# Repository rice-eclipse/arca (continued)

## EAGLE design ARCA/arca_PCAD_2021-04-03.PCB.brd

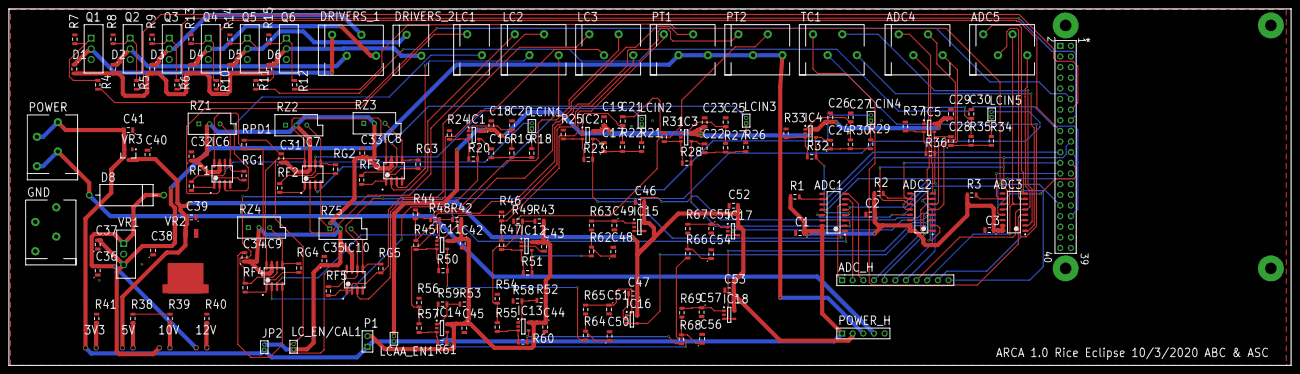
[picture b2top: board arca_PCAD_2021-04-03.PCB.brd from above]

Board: 2 copper layers, 306.1 x 85.1 mm, 197 parts (0 on the bottom side), 114 nets.

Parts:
3V3: LED5MM; LED5MM_1PRIMARY
5V: LED5MM; LED5MM_4PRIMARY
10V: LED5MM; LED5MM_3PRIMARY
12V: LED5MM; LED5MM_2PRIMARY
*: raspberry_pi; HDR2X20_1PRIMARY
ADC1, ADC2, ADC3: MCP3208; SOIC127P600X175-16N_1PRIMARY
ADC4, ADC5: PTSA_1,5/_4-3,5-Z_-_1985218; 4PINCANCONNECTOR_1PRIMARY
ADC_H: Header_11; HDR1X11_1PRIMARY
C1, C2, C3, C39: Cap; CAPCP2012X06N_3PRIMARY
C16: 1nF; CAPCP2012X06N_16PRIMARY
C17, C21, C22, C24: 1nF; CAPCP2012X06N_14PRIMARY
C18: 0.1UF; CAPCP2012X06N_15PRIMARY
C19, C23, C26: 0.1UF; CAPCP2012X06N_14PRIMARY
C20: 1nF; CAPCP2012X06N_15PRIMARY
C25, C27: 1nF; CAPCP2012X06N_13PRIMARY
C28: 1nF; CAPCP2012X06N_11PRIMARY
C29: 0.1UF; CAPCP2012X06N_11PRIMARY
C30: 1nF; CAPCP2012X06N_12PRIMARY
C31: 1UF; CAPCP2012X06N_11PRIMARY
C32: 1UF; CAPCP2012X06N_2PRIMARY
C33: 1UF; CAPCP2012X06N_10PRIMARY
C34: 1UF; CAPCP2012X06N_9PRIMARY
C35: 1UF; CAPCP2012X06N_8PRIMARY
C36, C37, C38: Cap; CAPCP2012X06N_2PRIMARY
C40: Cap; CAPCP2012X06N_7PRIMARY
C41: Cap; CAPCP2012X06N_6PRIMARY
C42, C43, C44, C45: 0.1UF; CAPCP2012X06N_1PRIMARY
C46: 0.1UF; CAPCP2012X06N_5PRIMARY
C47, C52, C53: 0.1UF; CAPCP2012X06N_3PRIMARY
C48: 68nF; CAPCP2012X06N_4PRIMARY
C49, C51, C55, C57: 680pF; CAPCP2012X06N_1PRIMARY
C50, C54, C56: 68nF; CAPCP2012X06N_2PRIMARY
D1, D2, D3, D4, D5, D6: Diode; DIOC2012X06N_1PRIMARY
D8: Diode; DIODE-0.7_1PRIMARY
DRIVERS_1: 1991118; 4PINCANCONNECTOR_1PRIMARY
DRIVERS_2: 0; 2POS_GREEN_BOI_1PRIMARY
DUMMY1, DUMMY2, DUMMY3, DUMMY4: P:EX244Y244D1081
GND: 1991118; 4PINCANCONNECTOR_1PRIMARY
IC1, IC2, IC4: LMV321LICTRT; SOT95P245X110-5N_6PRIMARY
IC3: LMV321LICTRT; SOT95P245X110-5N_7PRIMARY
IC5: LMV321LICTRT; SOT95P245X110-5N_5PRIMARY
IC6, IC8, IC9, IC10: MCP6N11R; SOIC127P1030X265-8N_1PRIMARY
IC7: MCP6N11R; SOIC127P1030X265-8N_2PRIMARY
IC11: LMV321LICTRT; SOT95P245X110-5N_4PRIMARY
IC12, IC13, IC14, IC15, IC17: LMV321LICTRT; SOT95P245X110-5N_2PRIMARY
IC16: LMV321LICTRT; SOT95P245X110-5N_3PRIMARY
IC18: LMV321LICTRT; SOT95P245X110-5N_1PRIMARY
JP2: PINHD-1X2; MHDR1X2_4PRIMARY
LC1: 0; 2POS_GREEN_BOI_2PRIMARY
LC2: 1991118; 4PINCANCONNECTOR_6PRIMARY
LC3: 1991118; 4PINCANCONNECTOR_5PRIMARY
LCAA_EN1: PINHD-1X2; MHDR1X2_3PRIMARY
LCIN1: PINHD-1X2; MHDR1X2_4PRIMARY
LCIN2, LCIN3: PINHD-1X2; MHDR1X2_3PRIMARY
LCIN4: PINHD-1X2; MHDR1X2_2PRIMARY
LCIN5: PINHD-1X2; MHDR1X2_1PRIMARY
LC_EN/CAL1: PINHD-1X2; MHDR1X2_4PRIMARY
P1: Header_2; HDR1X2_1PRIMARY
POWER: 1991118; 4PINCANCONNECTOR_1PRIMARY
POWER_H: Header_5; HDR1X5_1PRIMARY
PT1: 1991118; 4PINCANCONNECTOR_4PRIMARY
PT2: 1991118; 4PINCANCONNECTOR_3PRIMARY
Q1, Q2, Q3, Q4, Q5, Q6: FQP30N06L-ND; UA78M_1PRIMARY
R1, R2, R3: Res1; RESC_0805_2012_6PRIMARY
R4, R5, R6, R10, R11, R12: Res1; RESC_0805_2012_8PRIMARY
R7: Res1; RESC_0805_2012_1PRIMARY
R8, R9, R13, R14, R15: Res1; RESC_0805_2012_17PRIMARY
R18: 24.7K; RESC_0805_2012_11PRIMARY
R19: 164K; RESC_0805_2012_16PRIMARY
R20: 50.6K; RESC_0805_2012_8PRIMARY
R21: 24.7K; RESC_0805_2012_15PRIMARY
R22: 164K; RESC_0805_2012_14PRIMARY
R23, R28, R32, R36: 50.6K; RESC_0805_2012_6PRIMARY
R24, R25, R37: 12.6K; RESC_0805_2012_2PRIMARY
R26: 24.7K; RESC_0805_2012_2PRIMARY
R27: 164K; RESC_0805_2012_1PRIMARY
R29: 24.7K; RESC_0805_2012_13PRIMARY
R30: 164K; RESC_0805_2012_12PRIMARY
R31, R33: 12.6K; RESC_0805_2012_11PRIMARY
R34: 24.7K; RESC_0805_2012_10PRIMARY
R35: 164K; RESC_0805_2012_9PRIMARY
R38: 140; RESC_0805_2012_2PRIMARY
R39: 470; RESC_0805_2012_1PRIMARY
R40: 530; RESC_0805_2012_1PRIMARY
R41: 39; RESC_0805_2012_2PRIMARY
R42, R43, R53: 20K; RESC_0805_2012_6PRIMARY
R44, R46, R56: 22; RESC_0805_2012_1PRIMARY
R45, R47, R55, R57: 20K; RESC_0805_2012_2PRIMARY
R48, R49, R58, R59: 3K; RESC_0805_2012_6PRIMARY
R50, R51, R60, R61: 150K; RESC_0805_2012_6PRIMARY
R52: 20K; RESC_0805_2012_8PRIMARY
R54: 22; RESC_0805_2012_7PRIMARY
R62, R64, R66, R68: 1.5K; RESC_0805_2012_1PRIMARY
R63, R65, R67, R69: 150K; RESC_0805_2012_1PRIMARY
RF1, RF3, RF4: 20K; RESC_0805_2012_1PRIMARY
RF2: 20K; RESC_0805_2012_4PRIMARY
RF5: 20K; RESC_0805_2012_5PRIMARY
RG1, RG3, RG4: 200; RESC_0805_2012_1PRIMARY
RG2: 200; RESC_0805_2012_4PRIMARY
RG5: 200; RESC_0805_2012_3PRIMARY
RPD1: 20K; RESC_0805_2012_2PRIMARY
RZ1, RZ3, RZ4: RPot; VR5_2PRIMARY
RZ2: RPot; VR5_3PRIMARY
RZ5: RPot; VR5_1PRIMARY
TC1: 1991118; 4PINCANCONNECTOR_2PRIMARY
VR1: UA78M; UA78M_1PRIMARY
VR2: LM1084ISX-5.0/NOPB; LM1084ISX-5.0/NOPB_1PRIMARY
VR3: AP2210N-3.3TRG1; SOT95P245X110-3N_1PRIMARY

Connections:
+3V3: 3V3.1, C1.1, JP2.1, LCAA_EN1.1, P1.1
+3V3_LC: C31.1, C32.1, C33.1, C34.1, C35.1, IC6.7, IC7.7, IC8.7, IC9.7, IC10.7, JP2.2, LC_EN/CAL1.1, RZ1.2, RZ2.2, RZ3.2, RZ4.2, RZ5.2
+3V3_LCAA: C18.1, C19.1, C23.1, C26.1, C29.1, IC1.5, IC2.5, IC3.5, IC4.5, IC5.5, LCAA_EN1.2
+3V3_PT: C42.1, C43.1, C44.1, C45.1, IC11.5, IC12.5, IC13.5, IC14.5, P1.2, R42.1, R43.1, R52.1, R53.1
+5V: 5V.1, C39.2, C40.2, C46.1, C47.1, C52.1, C53.1, IC15.5, IC16.5, IC17.5, IC18.5, POWER_H.2, VR2.2, VR3.3
+10V: 10V.1, C37.2, C38.2, POWER_H.3, VR1.3
+12: D1.2, D2.2, D3.2, D4.2, D5.2, D6.2
ADC1_A5: ADC1.6, ADC_H.1
ADC1_A6: ADC1.7, ADC_H.2
ADC1_A7: ADC1.8, ADC_H.3
ADC1_CS: *.22, ADC1.10, R1.1
ADC2_A4: ADC2.5, ADC_H.4
ADC2_A7: ADC2.8, ADC_H.7
ADC2_CS: *.24, ADC2.10, R2.1
ADC3_A4: ADC3.5, ADC_H.8
ADC3_CS: *.26, ADC3.10, R3.1
CAL: IC6.8, IC7.8, IC8.8, IC9.8, IC10.8, LC_EN/CAL1.2, RPD1.1
DRIVER_1: *.11, R4.1
DRIVER_1_NEGATIVE: D1.1, Q1.2
DRIVER_2: *.13, R5.1
DRIVER_2_NEGATIVE: D2.1, Q2.2
DRIVER_3: *.15, R6.1
DRIVER_3_NEGATIVE: D3.1, Q3.2
DRIVER_4: *.18, R10.1
DRIVER_4_NEGATIVE: D4.1, Q4.2
DRIVER_5: *.33, R11.1
DRIVER_5_NEGATIVE: D5.1, DRIVERS_2.1, Q5.2
DRIVER_6: *.32, R12.1
DRIVER_6_NEGATIVE: D6.1, DRIVERS_2.2, Q6.2
GND: C36.1, C38.1, GND.1, GND.2, GND.3, GND.4, R38.2, R39.1, R40.1, R41.2
LC1: ADC1.1, C16.2, IC1.4, R20.1
LC1_OUT_N: IC6.2, LC1.1
LC1_OUT_P: IC6.3, LC1.2
LC1_PREC: IC6.6, LCIN1.2, RF1.1
LC2: ADC1.2, C17.2, IC2.4, R23.1
LC2_PREC: IC7.6, LCIN2.2, RF2.1
LC3: ADC1.3, C22.2, IC3.4, R28.1
LC3_PREC: IC8.6, LCIN3.2, RF3.1
LC4: ADC1.4, C24.2, IC4.4, R32.1
LC4_PREC: IC9.6, LCIN4.2, RF4.1
LC5: ADC1.5, C28.2, IC5.4, R36.1
LC5_OUT_N: IC10.1, IC10.2, RF5.2, RG5.2
LC5_PREC: IC10.6, LCIN5.2, RF5.1
MISO: *.21, ADC1.12, ADC2.12, ADC3.12
MOSI: *.19, ADC1.11, ADC2.11, ADC3.11
NET3V3_K: 3V3.2, R41.1
NET5V_K: 5V.2, R38.1
NET10V_K: 10V.2, R39.2
NET12V_A: 12V.1, C36.2, D8.2, VR1.1
NET12V_K: 12V.2, R40.2
NETC16_1: C16.1, R18.1, R19.2
NETC17_1: C17.1, R21.1, R22.2
NETC20_1: C20.1, IC1.1, R19.1
NETC21_1: C21.1, IC2.1, R22.1
NETC22_1: C22.1, R26.1, R27.2
NETC24_1: C24.1, R29.1, R30.2
NETC25_1: C25.1, IC3.1, R27.1
NETC27_1: C27.1, IC4.1, R30.1
NETC28_1: C28.1, R34.1, R35.2
NETC30_1: C30.1, IC5.1, R35.1
NETC48_1: C48.1, R62.1, R63.2
NETC49_1: C49.1, IC15.1, R63.1
NETC50_1: C50.1, R64.1, R65.2
NETC51_1: C51.1, IC16.1, R65.1
NETC54_1: C54.1, R66.1, R67.2
NETC55_1: C55.1, IC17.1, R67.1
NETC56_1: C56.1, R68.1, R69.2
NETC57_1: C57.1, IC18.1, R69.1
NETIC1_3: IC1.3, R20.2, R24.1
NETIC2_3: IC2.3, R23.2, R25.1
NETIC3_3: IC3.3, R28.2, R31.1
NETIC4_3: IC4.3, R32.2, R33.1
NETIC5_3: IC5.3, R36.2, R37.1
NETIC6_1: IC6.1, RF1.2, RG1.2
NETIC6_5: IC6.5, RG1.1, RZ1.3
NETIC7_1: IC7.1, RF2.2, RG2.2
NETIC7_5: IC7.5, RG2.1, RZ2.3
NETIC8_1: IC8.1, RF3.2, RG3.2
NETIC8_5: IC8.5, RG3.1, RZ3.3
NETIC9_1: IC9.1, RF4.2, RG4.2
NETIC9_5: IC9.5, RG4.1, RZ4.3
NETIC10_5: IC10.5, RG5.1, RZ5.3
NETIC11_1: IC11.1, R42.2, R48.1
NETIC11_3: IC11.3, R45.1, R50.2
NETIC12_1: IC12.1, R43.2, R49.1
NETIC12_3: IC12.3, R47.1, R51.2
NETIC13_1: IC13.1, R52.2, R58.1
NETIC13_3: IC13.3, R55.1, R60.2
NETIC14_1: IC14.1, R53.2, R59.1
NETIC14_3: IC14.3, R57.1, R61.2
NETLCIN1_1: LCIN1.1, R18.2
NETLCIN2_1: LCIN2.1, R21.2
NETLCIN3_1: LCIN3.1, R26.2
NETLCIN4_1: LCIN4.1, R29.2
NETLCIN5_1: LCIN5.1, R34.2
NETQ1_1: Q1.1, R4.2, R7.2
NETQ2_1: Q2.1, R5.2, R8.2
NETQ3_1: Q3.1, R6.2, R9.2
NETQ4_1: Q4.1, R10.2, R13.2
NETQ5_1: Q5.1, R11.2, R14.2
NETQ6_1: Q6.1, R12.2, R15.2
PT1: ADC2.1, IC16.3, IC16.4
PT1_OUT: R44.2, R45.2
PT1_PREC: IC11.4, R50.1, R64.2
PT2: ADC2.2, IC15.3, IC15.4
PT2_OUT: R46.2, R47.2
PT2_PREC: IC12.4, R51.1, R62.2
PT3: ADC2.3, IC18.3, IC18.4
PT3_OUT: R54.2, R55.2
PT3_PREC: IC13.4, R60.1, R68.2
PT4: ADC2.4, IC17.3, IC17.4
PT4_OUT: R56.2, R57.2
PT4_PREC: IC14.4, R61.1, R66.2
SCK: *.23, ADC1.13, ADC2.13, ADC3.13

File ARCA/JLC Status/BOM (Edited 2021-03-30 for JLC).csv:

Quantity,Designator,Footprint,Comment,LCSC Part #,Description
3,"ADC1, ADC2, ADC3",,MCP3208,C16939,
9,"C1, C2, C3, C36, C37, C38, C39, C40, C41",CAPCP2012X06N,1u,C28323,Capacitor
10,"C16, C17, C20, C21, C22, C24, C25, C27, C28, C30",CAPCP2012X06N,1nF,C46653,"CAPACITOR, American symbol"
13,"C18, C19, C23, C26, C29, C42, C43, C44, C45, C46, C47, C52, C53",CAPCP2012X06N,0.1UF,C49678,"CAPACITOR, American symbol"
5,"C31, C32, C33, C34, C35",CAPCP2012X06N,1UF,C28323,"CAPACITOR, American symbol"
4,"C48, C50, C54, C56",CAPCP2012X06N,68nF,C1756,"CAPACITOR, American symbol"
4,"C49, C51, C55, C57",CAPCP2012X06N,680pF,C53150,"CAPACITOR, American symbol"
6,"D1, D2, D3, D4, D5, D6",DIOC2012X06N,Diode,C147278,Default Diode
13,"IC1, IC2, IC3, IC4, IC5, IC11, IC12, IC13, IC14, IC15, IC16, IC17, IC18",SOT95P245X110-5N,LMV321LICTRT,C7972,"High Performance, 145 MHz FastFET Op AmpsSource: http://www.analog.com/static/imported-files/data_sheets/AD80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"
5,"IC6, IC7, IC8, IC9, IC10",SOIC127P1030X265-8N,MCP6N11R,C144213,"Low Cost, Low Power, Instrumentation AmplifierSource: http://www.analog.com/UploadedFiles/Data_Sheets/377933300239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"
15,"R1, R2, R3, R4, R5, R6, R7, R8, R9, R10, R11, R12, R13, R14, R15",RESC_0805_2012,2k,C17604,Resistor
5,"R18, R21, R26, R29, R34",RESC_0805_2012,25k,C63863,"RESISTOR, American symbol"
5,"R19, R22, R27, R30, R35",RESC_0805_2012,162k,C17486,"RESISTOR, American symbol"
5,"R20, R23, R28, R32, R36",RESC_0805_2012,50k,C63865,"RESISTOR, American symbol"
5,"R24, R25, R31, R33, R37",RESC_0805_2012,13k,C17455,"RESISTOR, American symbol"
1,R38,RESC_0805_2012,140,C17464,"RESISTOR, American symbol"
1,R39,RESC_0805_2012,470,C17710,"RESISTOR, American symbol"
1,R40,RESC_0805_2012,530,C17734,"RESISTOR, American symbol"
1,R41,RESC_0805_2012,39,C17659,"RESISTOR, American symbol"
14,"R42, R43, R45, R47, R52, R53, R55, R57, RF1, RF2, RF3, RF4, RF5, RPD1",RESC_0805_2012,20K,C4328,"RESISTOR, American symbol"
4,"R44, R46, R54, R56",RESC_0805_2012,22,C17561,"RESISTOR, American symbol"
4,"R48, R49, R58, R59",RESC_0805_2012,3K,C17661,"RESISTOR, American symbol"
8,"R50, R51, R60, R61, R63, R65, R67, R69",RESC_0805_2012,150K,C17470,"RESISTOR, American symbol"
4,"R62, R64, R66, R68",RESC_0805_2012,1.5K,C4310,"RESISTOR, American symbol"
5,"RG1, RG2, RG3, RG4, RG5",RESC_0805_2012,200,C17540,"RESISTOR, American symbol"
1,VR3,SOT95P245X110-3N,AP2210N-3.3TRG1,C155508,3.3V regulator300mA rating.

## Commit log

2020-01-03 hardware files
2020-01-18 Update .gitignore for Altium
2020-01-18 Remove ignored directories
2020-01-18 Remove Previews subdirectory
2020-01-18 dded missing files
2020-01-18 Attempt 2 at fixing things
2020-01-18 Fix PrjPCB attempt
2020-01-18 adc sch
2020-01-25 removed duplicate adc sch
2020-01-25 adc_sch done
2020-01-25 LC Sch done
2020-01-25 duplicate relay sch deleted
2020-01-25 pt sch renames
2020-01-25 duplicate test point sch deleted
2020-01-25 ignitor mods
2020-01-25 added connector page
2020-01-26 added connectors and broke out adcs
2020-01-26 con done
2020-01-26 grounded pi
2020-01-26 heating tape mock up
2020-02-01 fourth solenoid circuit removed
2020-02-08 driver circuit added, old drivers Free
2020-02-08 sch done? :D
2020-02-08 top level removed
2020-02-08 prelayout clean up
2020-02-09 cleaned power sch
2020-02-16 re annotated designators and addressed some erc errors
2020-03-07 ready for layout :)
2020-03-07 okay, now its layout time; errors be gone
2020-03-08 some layouts :D
2020-03-09 initial layout!
2020-04-11 pin inconsistency btwn sch and pcb fixed
2020-04-11 initial traces
2020-04-18 Add more traces
2020-04-18 Update ADC pin numbers in schlib
2020-04-18 Update ADC SCH with new pin numbers
2020-04-18 Fix ADC pins in PCB
2020-04-18 some ics routed
2020-05-20 more traces added
2020-05-20 added headers for power and extra adc channel breakout
2020-05-20 more traces for sensors
2020-05-20 failed attempts to fix adc
2020-05-20 adcs given back footprint of sop64
2020-05-27 link btwn adc and footprint fixed and some tracin
2020-05-27 some adc traces routed
2020-05-27 Add more adc to header traces
2020-05-27 route ADC spi
2020-05-27 Fix driver nets and route
2020-05-27 PrjPCB update
2020-05-29 Add BOM document
2020-06-04 auto route finished traces?
2020-06-04 poly pours added
2020-06-04 Fix pour over GND traces
2020-06-04 Design rules
2020-06-11 acid trap reduction from auto route
2020-06-12 exports added to prj
2020-06-18 Add grounded mounting holes
2020-06-25 breakout mounting holes
2020-06-25 holes moved
2020-06-25 jk now theyre moved
2020-07-21 untangled raspberry pi connections
2020-07-21 first draft
2020-07-22 drc mods
2020-09-12 this is probably the most right version
2020-09-19 fixed raspberry pi issues, very few design rule check errors left!
2020-09-25 -bad adcs but good drc
2020-09-25 new old adcs added, still need routing
2020-10-03 new old adcs traced in
2020-10-03 happier drc
2020-10-03 happiest drc! order time!
2020-10-03 hell yeah; order time
2020-10-03 board outline added
2020-10-03 board labeled
2020-10-03 logo added to board
2020-10-03 correct ouputs added
2021-03-28 most recent arca file and eagle exported mk1-1 with notes
2021-03-30 AAAAAAAAAAAAAAAAAAAAAAAAAA
2021-03-30 MORE AAAAAAA
2021-03-30 BOM work
2021-03-30 updated names + included edited BOM
2021-03-31 PNP created
2021-04-02 Fixed PCAD (still have not exported CAM)
2021-10-30 starting arca 2.0 voltage regulators
2021-10-30 rough vr layout
2021-10-30 made diode-ss less ugly
2021-11-03 drivers
2021-11-04 started on LC work
2021-11-04 fixed incorrect feedback on LC inamp
2021-11-07 rip 3.3v
2021-11-07 more compact drivers
2021-11-12 concept for PTs
2021-11-19 now with 10x gain on PTs
2021-11-19 board relay concept
2021-11-30 updating board with results from data analysis
2021-11-30 ADCs now added
2021-11-30 raspberry pi pinouts
2021-11-30 some preliminary routing - ready for autorouter?
2021-12-01 first rev of board
2022-01-04 resistor cleanup for v_ref
2022-01-04 throwing together some reference docs
2022-01-20 separate fuses for each external connection + LM324s on +10V
2022-01-26 laying out extra breakers in board
2022-02-05 heartbeat light
2022-02-08 found issues with connector orientation
2022-02-08 solid model referencing has revealed incorrectly sized connectors
2022-02-12 bigger 5mm connectors
2022-02-12 routing on shrunken board
2022-02-19 final revisions on board before design review
2022-02-25 values tweaks as we make a BOM
2022-03-01 slight reshaping of schematic to make more human-readable
2022-03-04 add connector for router
2022-03-04 move to potentiometers for load cells
2022-03-05 cheaper fuses
2022-03-20 preparing CAM
